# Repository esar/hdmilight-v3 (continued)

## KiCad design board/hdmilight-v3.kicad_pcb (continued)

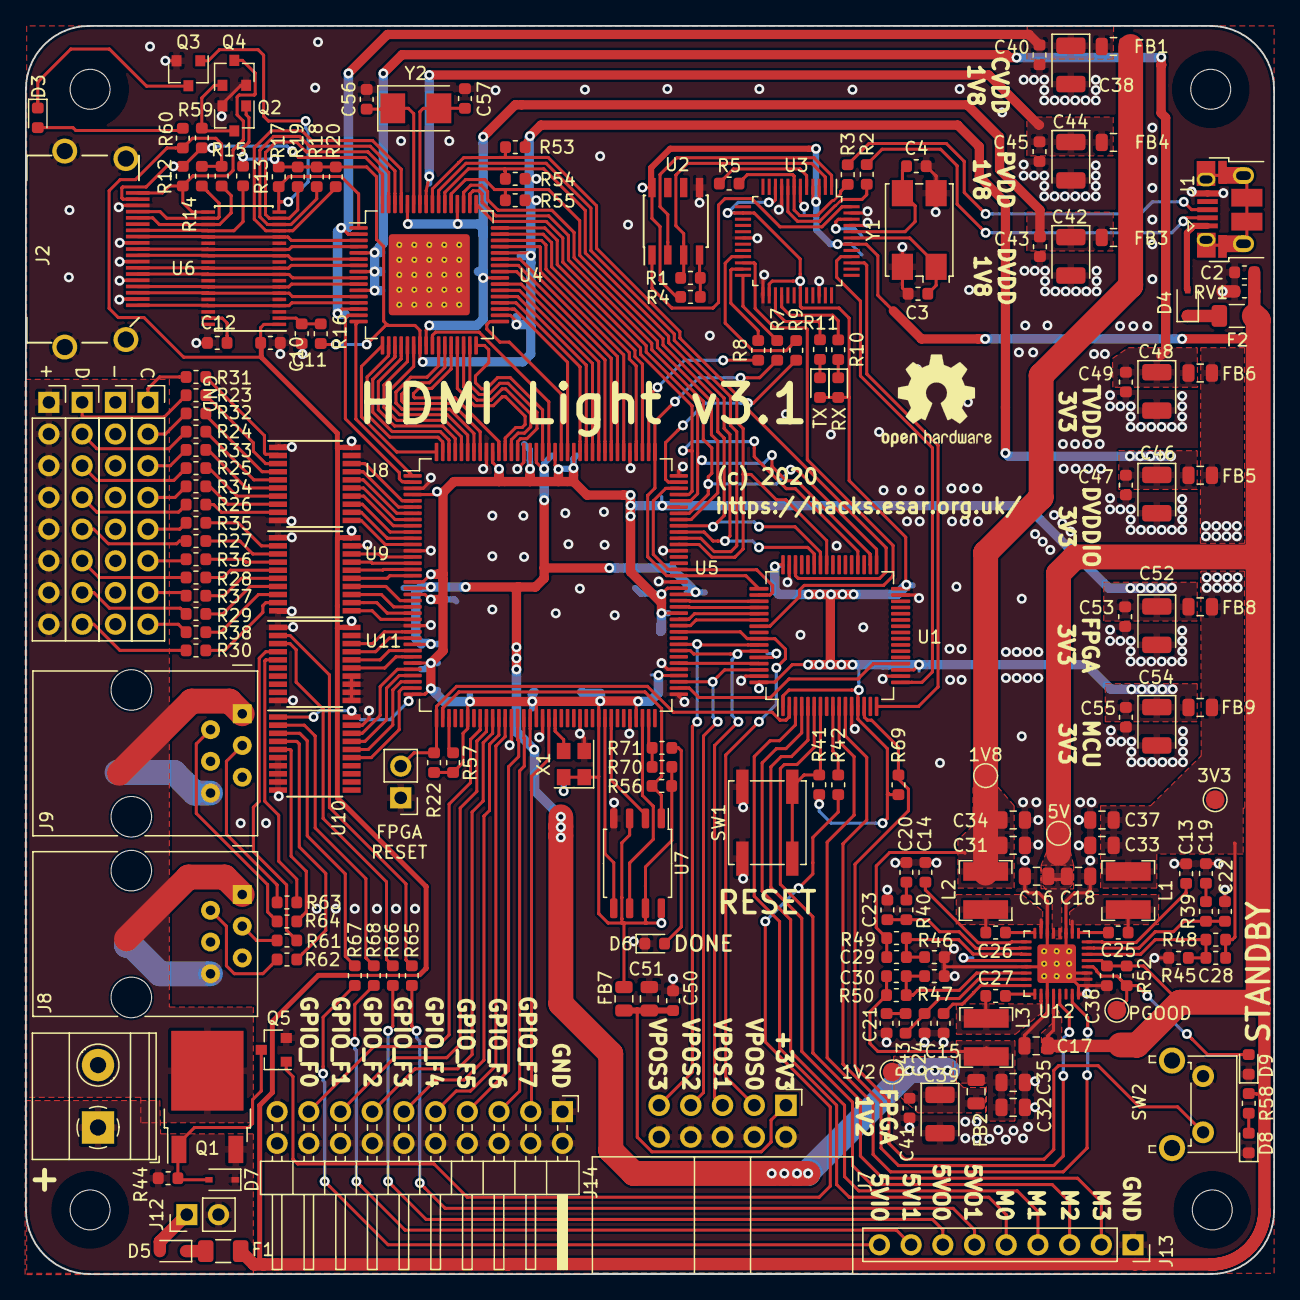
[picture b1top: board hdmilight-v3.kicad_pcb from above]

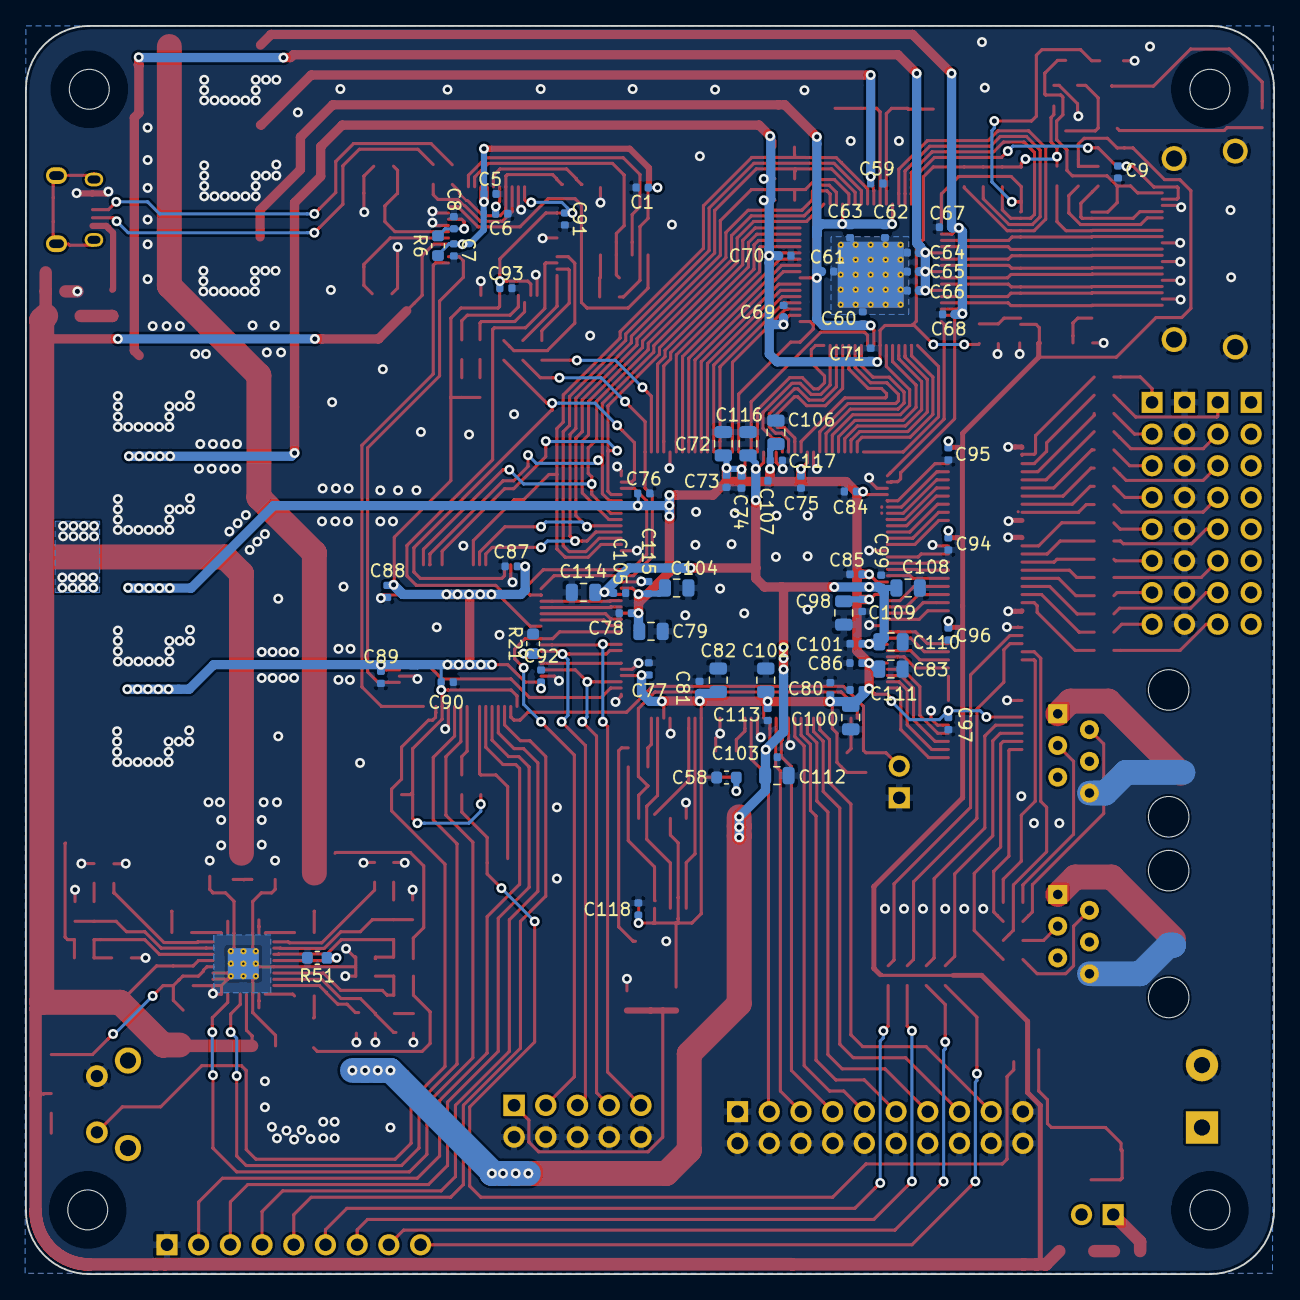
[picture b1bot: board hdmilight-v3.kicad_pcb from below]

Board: 2 copper layers, 100.0 x 100.0 mm, 259 parts (70 on the bottom side), 239 nets.

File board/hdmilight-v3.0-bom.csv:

Designator,Package,Quantity,Designation,Part #,Farnell #,Unit GBP,Total GBP
"C116,C114,C112,C110,C108,C106,C104,C102,C100,C98,C72,C83,C82,C79",C_0805_2012Metric,14,4.7uF,,,,0
"C117,C115,C113,C111,C109,C107,C105,C103,C101,C99,C86,C85,C84,C81,C80,C78,C77,C76,C75,C74,C73",C_0402_1005Metric,21,0.47uF,,,,0
"C19,C20,C21",C_0603_1608Metric,3,1nF,,,,0
"C22,C23,C24,C28,C29,C30",C_0603_1608Metric,6,DNI,,,,0
"C25,C26,C27",C_0603_1608Metric,3,0.047uF,,,,0
"C3,C4",C_0603_1608Metric,2,12pF,,,,0
C36,C_0603_1608Metric,1,2.2uF,,,,0
C37,C_0805_2012Metric,1,DNI,,,,0
"C38,C39,C42,C44,C46,C48,C52,C54",CP_EIA-3528-21_Kemet-B,8,33uF,Kemet: T491B336K006AT,2408593,0.396,3.168
"C50,C2,C10,C11,C12,C13,C14,C15,C40,C41,C43,C45,C47,C49,C53,C55",C_0603_1608Metric,16,0.1uF,,,,0
"C51,C16,C17,C18,C31,C32,C33,C34,C35",C_0805_2012Metric,9,22uF,TDK: C2012X5R1A226M085AC,2526256,0.493,4.437
"C57,C56",C_0603_1608Metric,2,18pF,,,,0
C58,C_0603_1608Metric,1,0.01uF,,,,0
"C9,C118,C1,C97,C96,C95,C94,C8,C6,C93,C91,C7,C5,C92,C90,C89,C88,C87,C71,C70,C69,C68,C67,C66,C65,C64,C63,C62,C61,C60,C59",C_0402_1005Metric,31,0.1uF,,,,0
"D5,D4",D_SOD-323,2,2A,"NXP: PMEG3020EJ,115",1757772,0.332,0.664
"D6,D3,D1,D2",LED_0603_1608Metric,4,LED,Kingbright: KPT-1608EC,2099221,0.107,0.428
D7,D_SOD-323,1,5V1,On Semi: MM3Z5V1ST1G,2317476,0.098,0.098
"F2,F1",Fuse_1206_3216Metric,2,1206L050,Littelfuse: 1206L050YR,1596993,0.285,0.57
"FB7,FB1,FB2,FB3,FB4,FB5,FB6,FB8,FB9",L_0805_2012Metric,9,22ohm@100MHz,Murata: BLM21PG220SN1D,1515659,0.055,0.495
J1,USB_Micro-B_Amphenol_10103594-0001LF_Horizontal,1,USB_B_Micro,Amphenol: 10103594-0001LF,2293752,0.44,0.44
"J10,J6,J5,J4",PinSocket_1x08_P2.54mm_Vertical,4,Conn_01x08,Multicomp: 2212S-08SG-85,1593463,0.17,0.68
J11,"TerminalBlock_Phoenix_MKDS-1,5-2_1x02_P5.00mm_Horizontal",1,Screw_Terminal_01x02,"Phoenix: MKDS 1,5/2",3714240,1.05,1.05
J12,PinHeader_1x02_P2.54mm_Horizontal,1,Conn_01x02_Male,Multicomp: MC34745,1593426,0.017,0.017
J13,PinHeader_1x16_P2.54mm_Horizontal,1,Conn_01x16_Male,Wurth: 61301611021,2356187,0.661,0.661
J2,HDMI_SOCKET_FCI_10029449,1,HDMI_A,Amphenol/FCI: 10029449-001RLF,2112524,1.22,1.22
J3,PinHeader_1x02_P2.54mm_Vertical,1,Conn_01x02_Male,Multicomp: 2211S-02G,1593411,0.011,0.011
J7,PinHeader_2x05_P2.54mm_Vertical,1,Conn_02x05_Odd_Even,Muticomp: 2213S-10G,1593442,0.053,0.053
"J8,J9",RJ12_Amphenol_54601,2,6P6C,Amphenol: 54601-906WPLF,2135977,0.265,0.53
"L1,L2",L_Bourns-SRN4018,2,4.7uH/2.1A,TDK: SPM4020T-4R7M-LR,2564035,1.52,3.04
L3,L_Bourns-SRN4018,1,2.2uH/3.5A,TDK: SPM4015T-2R2M-LR,2564023,0.342,0.342
Q1,TO-252-2,1,FDD6530A,On Semi: FDD6530A,3003908,0.759,0.759
"Q2,Q4,Q3",SOT-23,3,BSS123,On Semi: BSS123,9845321,0.254,0.762
R13,R_0603_1608Metric,1,27K,,,,0
"R14,R15,R18,R19,R20,R48,R51",R_0603_1608Metric,7,47K,,,,0
"R2,R3",R_0603_1608Metric,2,27R,,,,0
"R21,R1",R_0603_1608Metric,2,2K2,,,,0
R39,R_0603_1608Metric,1,15K,,,,0
R40,R_0603_1608Metric,1,33K,,,,0
R42,R_0603_1608Metric,1,150R,,,,0
R43,R_0603_1608Metric,1,18K,,,,0
R49,R_0603_1608Metric,1,20K,,,,0
R5,R_0603_1608Metric,1,1K5,,,,0
"R55,R54,R53",R_0603_1608Metric,3,4K7,,,,0
"R57,R56,R69,R44,R41,R4,R16,R45,R46,R47,R50,R52,R22",R_0603_1608Metric,13,10K,,,,0
"R59,R17",R_0603_1608Metric,2,100K,,,,0
R6,R_0603_1608Metric,1,470R,,,,0
"R68,R67,R66,R65,R64,R63,R62,R61,R23,R24,R25,R26,R27,R28,R29,R30,R31,R32,R33,R34,R35,R36,R37,R38",R_0603_1608Metric,24,82R,,,,0
"R7,R8,R9",R_0603_1608Metric,3,68R,,,,0
R70,R_0603_1608Metric,1,330R,,,,0
"R71,R60,R10,R11,R12",R_0603_1608Metric,5,1K,,,,0
RV1,R_0603_1608Metric,1,V5.5MLA0603H,Littelfuse: V5.5MLA0603H,1757273,0.36,0.36
SW1,SW_SPST_B3S-1000,1,SW_Push,Omron: B3S-1000,177807,0.535,0.535
SW2,SW_Tactile_SPST_Angled_PTS645Vx31-2LFS,1,SW_Push,C&K: PTS645VH58-2LFS,2320088,0.201,0.201
U1,LQFP-64_10x10mm_P0.5mm,1,STM32F303RETx,ST Micro: STM32F303RET6,2466939,6.56,6.56
U12,QFN-32-1EP_5x5mm_P0.5mm_EP3.1x3.1mm_ThermalVias,1,TPS65266,Texas: TPS65266RHBT,2471151,3.92,3.92
U2,SOIC-8_3.9x4.9mm_P1.27mm,1,93CxxB,Microchip: 93C46BT-I/SN,1607557,0.18,0.18
U3,LQFP-48_7x7mm_P0.5mm,1,FT2232D,FTDI: FT2232D,1615843,5.7,5.7
U4,LQFP-64-1EP_10x10mm_P0.5mm_EP6.5x6.5mm_ThermalVias,1,ADV7611,Analog: ADV7611,,6.5,6.5
U5,TQFP-144_20x20mm_P0.5mm,1,XC6SLX9-TQG144,Xilinx: XC6SLX9-2TQG144C,2763358,14.91,14.91
U6,TSSOP-38_4.4x9.7mm_P0.5mm,1,TPD12S520,Texas: TPD12S520DBTR,3116492,1.19,1.19
U7,SOIC-8_3.9x4.9mm_P1.27mm,1,S25FL064L,Cypress: S25FL064LABMFI010,2768034,1.68,1.68
"U8,U9,U10,U11",TSSOP-20_4.4x6.5mm_P0.65mm,4,74LV245,Texas: SN74LV245APWR,2342392,0.626,2.504
X1,Oscillator_SMD_Abracon_ASE-4Pin_3.2x2.5mm,1,SG-310SCF-32MHz,Multicomp: MCSJK-3N-32.00-3.3-25-B,2854318,0.639,0.639
Y1,Crystal_SMD_7050-4Pin_7.0x5.0mm,1,6MHz / 12pF,Euroquartz: 6.000MHZ MQ/30/30/-40+90/12PF,1640909,1.73,1.73
Y2,Crystal_SMD_5032-2Pin_5.0x3.2mm,1,28.6363MHz / 18pF,TXC: 7A-28.63636MAAJ-T,1841958,0.665,0.665
TOTAL,,244,,,,,66.699

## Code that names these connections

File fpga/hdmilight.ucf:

## Prohibit the automatic placement of pins that are connected to VCC or GND for configuration.
CONFIG PROHIBIT=P69;
CONFIG PROHIBIT=P60;

# Crystal Clock - use 32MHz onboard oscillator
NET "CLK" LOC = "P56" | IOSTANDARD = LVTTL | PERIOD = 31.25ns ;

NET "ADV_AP" LOC = "P105" | IOSTANDARD = LVTTL;
NET "ADV_SCLK" LOC = "P104" | IOSTANDARD = LVTTL;
NET "ADV_LRCLK" LOC = "P102" | IOSTANDARD = LVTTL;
NET "ADV_MCLK" LOC = "P101" | IOSTANDARD = LVTTL;

NET "ADV_SCL" LOC = "P100" | IOSTANDARD = LVCMOS33;
NET "ADV_SDA" LOC = "P99" | IOSTANDARD = LVCMOS33;
NET "ADV_INT1" LOC = "P98" | IOSTANDARD = LVCMOS33;
NET "ADV_RST" LOC = "P97" | IOSTANDARD = LVCMOS33;

NET "ADV_HS" LOC = "P112" | IOSTANDARD = LVTTL;
NET "ADV_VS" LOC = "P111" | IOSTANDARD = LVTTL;
NET "ADV_DE" LOC = "P114" | IOSTANDARD = LVTTL;
NET "ADV_LLC" LOC = "P126" | IOSTANDARD = LVCMOS33;

NET "ADV_P<0>" LOC = "P115" | IOSTANDARD = LVCMOS33;
NET "ADV_P<1>" LOC = "P116" | IOSTANDARD = LVCMOS33;
NET "ADV_P<2>" LOC = "P117" | IOSTANDARD = LVCMOS33;
NET "ADV_P<3>" LOC = "P118" | IOSTANDARD = LVCMOS33;
NET "ADV_P<4>" LOC = "P119" | IOSTANDARD = LVCMOS33;
NET "ADV_P<5>" LOC = "P120" | IOSTANDARD = LVCMOS33;
NET "ADV_P<6>" LOC = "P121" | IOSTANDARD = LVCMOS33;
NET "ADV_P<7>" LOC = "P123" | IOSTANDARD = LVCMOS33;
NET "ADV_P<8>" LOC = "P124" | IOSTANDARD = LVCMOS33;
NET "ADV_P<9>" LOC = "P127" | IOSTANDARD = LVCMOS33;
NET "ADV_P<10>" LOC = "P131" | IOSTANDARD = LVCMOS33;
NET "ADV_P<11>" LOC = "P132" | IOSTANDARD = LVCMOS33;
NET "ADV_P<12>" LOC = "P133" | IOSTANDARD = LVCMOS33;
NET "ADV_P<13>" LOC = "P134" | IOSTANDARD = LVCMOS33;
NET "ADV_P<14>" LOC = "P137" | IOSTANDARD = LVCMOS33;
NET "ADV_P<15>" LOC = "P138" | IOSTANDARD = LVCMOS33;
NET "ADV_P<16>" LOC = "P139" | IOSTANDARD = LVCMOS33;
NET "ADV_P<17>" LOC = "P140" | IOSTANDARD = LVCMOS33;
NET "ADV_P<18>" LOC = "P141" | IOSTANDARD = LVCMOS33;
NET "ADV_P<19>" LOC = "P142" | IOSTANDARD = LVCMOS33;
NET "ADV_P<20>" LOC = "P143" | IOSTANDARD = LVCMOS33;
NET "ADV_P<21>" LOC = "P144" | IOSTANDARD = LVCMOS33;
NET "ADV_P<22>" LOC = "P1" | IOSTANDARD = LVCMOS33;
NET "ADV_P<23>" LOC = "P2" | IOSTANDARD = LVCMOS33;

NET "LED_OUT<0>" LOC = "P6" | IOSTANDARD = LVCMOS33 | DRIVE = 2 | SLEW = SLOW;
NET "LED_OUT<1>" LOC = "P8" | IOSTANDARD = LVCMOS33 | DRIVE = 2 | SLEW = SLOW;
NET "LED_OUT<2>" LOC = "P10" | IOSTANDARD = LVCMOS33 | DRIVE = 2 | SLEW = SLOW;
NET "LED_OUT<3>" LOC = "P12" | IOSTANDARD = LVCMOS33 | DRIVE = 2 | SLEW = SLOW;
NET "LED_OUT<4>" LOC = "P15" | IOSTANDARD = LVCMOS33 | DRIVE = 2 | SLEW = SLOW;
NET "LED_OUT<5>" LOC = "P17" | IOSTANDARD = LVCMOS33 | DRIVE = 2 | SLEW = SLOW;
NET "LED_OUT<6>" LOC = "P22" | IOSTANDARD = LVCMOS33 | DRIVE = 2 | SLEW = SLOW;
NET "LED_OUT<7>" LOC = "P24" | IOSTANDARD = LVCMOS33 | DRIVE = 2 | SLEW = SLOW;

NET "LED_CLK<0>" LOC = "P5"  | IOSTANDARD = LVCMOS33 | DRIVE = 2 | SLEW = SLOW;
NET "LED_CLK<1>" LOC = "P7" | IOSTANDARD = LVCMOS33 | DRIVE = 2 | SLEW = SLOW;
NET "LED_CLK<2>" LOC = "P9" | IOSTANDARD = LVCMOS33 | DRIVE = 2 | SLEW = SLOW;
NET "LED_CLK<3>" LOC = "P11" | IOSTANDARD = LVCMOS33 | DRIVE = 2 | SLEW = SLOW;
NET "LED_CLK<4>" LOC = "P14" | IOSTANDARD = LVCMOS33 | DRIVE = 2 | SLEW = SLOW;
NET "LED_CLK<5>" LOC = "P16" | IOSTANDARD = LVCMOS33 | DRIVE = 2 | SLEW = SLOW;
NET "LED_CLK<6>" LOC = "P21" | IOSTANDARD = LVCMOS33 | DRIVE = 2 | SLEW = SLOW;
NET "LED_CLK<7>" LOC = "P23" | IOSTANDARD = LVCMOS33 | DRIVE = 2 | SLEW = SLOW;

NET FLASH_CS LOC="P38"  | IOSTANDARD=LVTTL | DRIVE=8 | SLEW=FAST;
NET FLASH_CK LOC="P70"  | IOSTANDARD=LVTTL | DRIVE=8 | SLEW=FAST;
NET FLASH_SI LOC="P64"  | IOSTANDARD=LVTTL | DRIVE=8 | SLEW=FAST;
NET FLASH_SO LOC="P65"  | IOSTANDARD=LVTTL | DRIVE=8 | SLEW=FAST | PULLUP;

NET "MCU_SPI_CLK" LOC = "P88" | IOSTANDARD = LVCMOS33;
NET "MCU_SPI_MISO" LOC = "P87" | IOSTANDARD = LVCMOS33;
NET "MCU_SPI_MOSI" LOC = "P85" | IOSTANDARD = LVCMOS33;
NET "MCU_SPI_CS" LOC = "P74" | IOSTANDARD = LVCMOS33;

NET "MCU_PD2" LOC = "P84" | IOSTANDARD = LVCMOS33;
NET "MCU_PB8" LOC = "P78" | IOSTANDARD = LVCMOS33;

NET "VIVEPOS_SENSOR<0>" LOC = "P83";
NET "VIVEPOS_SENSOR<1>" LOC = "P80";
NET "VIVEPOS_SENSOR<2>" LOC = "P75";
NET "VIVEPOS_SENSOR<3>" LOC = "P81";

NET "PAPIX_POS<0>" LOC = "P34";
NET "PAPIX_POS<1>" LOC = "P35";

NET "PAPIX_RGB<0>" LOC = "P29" | IOSTANDARD=LVCMOS33;
NET "PAPIX_RGB<1>" LOC = "P30" | IOSTANDARD=LVCMOS33;

NET "IN5V<0>" LOC = "P33";
NET "IN5V<1>" LOC = "P32";

NET "OUT5V<0>" LOC = "P26" | IOSTANDARD=LVCMOS33;
NET "OUT5V<1>" LOC = "P27" | IOSTANDARD=LVCMOS33;

NET "GPIO<0>" LOC = "P44" | IOSTANDARD = LVCMOS33;
NET "GPIO<1>" LOC = "P45" | IOSTANDARD = LVCMOS33;
NET "GPIO<2>" LOC = "P46" | IOSTANDARD = LVCMOS33;
NET "GPIO<3>" LOC = "P47" | IOSTANDARD = LVCMOS33;
NET "GPIO<4>" LOC = "P48" | IOSTANDARD = LVCMOS33;
NET "GPIO<5>" LOC = "P50" | IOSTANDARD = LVCMOS33;
NET "GPIO<6>" LOC = "P51" | IOSTANDARD = LVCMOS33;
NET "GPIO<7>" LOC = "P55" | IOSTANDARD = LVCMOS33;

NET "ROUTE_UNDER<0>" LOC = "P93"; // JTAG_TDO
NET "ROUTE_UNDER<1>" LOC = "P92"; // JTAG_TCK


NET "ADV_LLC" TNM_NET = "ADV_LLC";
TIMESPEC "TS_ADV_LLC" = PERIOD "ADV_LLC" 6 ns HIGH 50%;
NET "ADV_P<0>" OFFSET = IN 2.7 ns VALID 3.5 ns BEFORE "ADV_LLC" RISING;
NET "ADV_P<1>" OFFSET = IN 2.7 ns VALID 3.5 ns BEFORE "ADV_LLC" RISING;
NET "ADV_P<2>" OFFSET = IN 2.7 ns VALID 3.5 ns BEFORE "ADV_LLC" RISING;
NET "ADV_P<3>" OFFSET = IN 2.7 ns VALID 3.5 ns BEFORE "ADV_LLC" RISING;
NET "ADV_P<4>" OFFSET = IN 2.7 ns VALID 3.5 ns BEFORE "ADV_LLC" RISING;
NET "ADV_P<5>" OFFSET = IN 2.7 ns VALID 3.5 ns BEFORE "ADV_LLC" RISING;
NET "ADV_P<6>" OFFSET = IN 2.7 ns VALID 3.5 ns BEFORE "ADV_LLC" RISING;
NET "ADV_P<7>" OFFSET = IN 2.7 ns VALID 3.5 ns BEFORE "ADV_LLC" RISING;
NET "ADV_P<8>" OFFSET = IN 2.7 ns VALID 3.5 ns BEFORE "ADV_LLC" RISING;
NET "ADV_P<9>" OFFSET = IN 2.7 ns VALID 3.5 ns BEFORE "ADV_LLC" RISING;
NET "ADV_P<10>" OFFSET = IN 2.7 ns VALID 3.5 ns BEFORE "ADV_LLC" RISING;
NET "ADV_P<11>" OFFSET = IN 2.7 ns VALID 3.5 ns BEFORE "ADV_LLC" RISING;
NET "ADV_P<12>" OFFSET = IN 2.7 ns VALID 3.5 ns BEFORE "ADV_LLC" RISING;
NET "ADV_P<13>" OFFSET = IN 2.7 ns VALID 3.5 ns BEFORE "ADV_LLC" RISING;
NET "ADV_P<14>" OFFSET = IN 2.7 ns VALID 3.5 ns BEFORE "ADV_LLC" RISING;
NET "ADV_P<15>" OFFSET = IN 2.7 ns VALID 3.5 ns BEFORE "ADV_LLC" RISING;
NET "ADV_P<16>" OFFSET = IN 2.7 ns VALID 3.5 ns BEFORE "ADV_LLC" RISING;
NET "ADV_P<17>" OFFSET = IN 2.7 ns VALID 3.5 ns BEFORE "ADV_LLC" RISING;
NET "ADV_P<18>" OFFSET = IN 2.7 ns VALID 3.5 ns BEFORE "ADV_LLC" RISING;
NET "ADV_P<19>" OFFSET = IN 2.7 ns VALID 3.5 ns BEFORE "ADV_LLC" RISING;
NET "ADV_P<20>" OFFSET = IN 2.7 ns VALID 3.5 ns BEFORE "ADV_LLC" RISING;
NET "ADV_P<21>" OFFSET = IN 2.7 ns VALID 3.5 ns BEFORE "ADV_LLC" RISING;
NET "ADV_P<22>" OFFSET = IN 2.7 ns VALID 3.5 ns BEFORE "ADV_LLC" RISING;
NET "ADV_P<23>" OFFSET = IN 2.7 ns VALID 3.5 ns BEFORE "ADV_LLC" RISING;

NET "ambilight/hscale4/COUNT(0)" TNM_NET = "MC_GRP_FFS";
TIMESPEC "TS_MC_GRP_FFS" = FROM "MC_GRP_FFS" TO "MC_GRP_FFS" TS_ADV_LLC*2;
#NET "ambilight/hscale4/COUNT(0)" TNM_NET = RAMS "MC_GRP_RAMS";
#TIMESPEC "TS_MC_GRP_RAMS" = FROM "MC_GRP_RAMS" TO "MC_GRP_RAMS" TS_ADV_LLC*2;

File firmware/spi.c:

#include <stdint.h>
#include <stm32f303xe.h>
#include <core_cm4.h>
#include "printf.h"
#include "spi.h"



void spiInit()
{
	// Configure pins
	// PC10 = SPI3_SCLK
	// PC11 = SPI3_MISO
	// PC12 = SPI3_MOSI
	// PA4  = SPI3_NSS

	// Enable GPIOA
	RCC->AHBENR |= RCC_AHBENR_GPIOAEN;

	// Enable GPIOC
	RCC->AHBENR |= RCC_AHBENR_GPIOCEN;

	// Set pins mode to alternate function
	GPIOA->MODER &= ~GPIO_MODER_MODER4;
	GPIOA->MODER |= 2 << GPIO_MODER_MODER4_Pos;
	GPIOC->MODER &= ~(GPIO_MODER_MODER10 | GPIO_MODER_MODER11 | GPIO_MODER_MODER12);
	GPIOC->MODER |= (2 << GPIO_MODER_MODER10_Pos) | (2 << GPIO_MODER_MODER11_Pos) | (2 << GPIO_MODER_MODER12_Pos);

	// Set alternate function to SPI3
	// PC10 = SPI3_SCLK = Alt Func 6
	// PC11 = SPI3_MISO = Alt Func 6
	// PC12 = SPI3_MOSI = Alt Func 6
	// PA4  = SPI3_NSS  = Alt Func 6
	GPIOA->AFR[0] &= ~GPIO_AFRL_AFRL4;
	GPIOA->AFR[0] |= 6 << GPIO_AFRL_AFRL4_Pos;
	GPIOC->AFR[1] &= ~(GPIO_AFRH_AFRH2 | GPIO_AFRH_AFRH3 | GPIO_AFRH_AFRH4);
	GPIOC->AFR[1] |= (6 << GPIO_AFRH_AFRH2_Pos) | (6 << GPIO_AFRH_AFRH3_Pos) | (6 << GPIO_AFRH_AFRH4_Pos);

	// Set the drive strength for the pins
	GPIOA->OSPEEDR &= ~GPIO_OSPEEDER_OSPEEDR4;
	GPIOA->OSPEEDR |= 2 << GPIO_OSPEEDER_OSPEEDR4_Pos;
	GPIOC->OSPEEDR &= ~(GPIO_OSPEEDER_OSPEEDR10 | GPIO_OSPEEDER_OSPEEDR11 | GPIO_OSPEEDER_OSPEEDR12);
	GPIOC->OSPEEDR |= (2 << GPIO_OSPEEDER_OSPEEDR10_Pos) | (2 << GPIO_OSPEEDER_OSPEEDR11_Pos) | (2 << GPIO_OSPEEDER_OSPEEDR12_Pos);

	// Enable pull-up on SPI3_NSS pin
	GPIOA->PUPDR |= 1 << GPIO_PUPDR_PUPDR4_Pos;

	// Enable SPI3 Clock
	RCC->APB1ENR |= RCC_APB1ENR_SPI3EN;

	// Disable SPI3 for configuration and reset
	SPI3->CR1 &= ~SPI_CR1_SPE;
	RCC->APB1RSTR |= RCC_APB1RSTR_SPI3RST;
	RCC->APB1RSTR &= ~RCC_APB1RSTR_SPI3RST;

	// Set clock rate, polarity and phase
	SPI3->CR1 = (4 << SPI_CR1_BR_Pos) | SPI_CR1_CPOL | SPI_CR1_CPHA;

	// Set as master
	SPI3->CR1 |= SPI_CR1_MSTR;

	// Set RX threshold to 8-bits 
	// If we don't then trying to receive an odd number of bytes never completes
	SPI3->CR2 |= SPI_CR2_SSOE | SPI_CR2_FRXTH;
}

void spiTransaction(void* txBuf1, int txBuf1Len,
                    void* txBuf2, int txBuf2Len,
                    void* rxBuf, int rxBufLen)
{
	volatile uint8_t dummy;

	SPI3->SR &= ~SPI_SR_MODF;
	SPI3->CR1 |= SPI_CR1_SPE;
	SPI3->CR1 |= SPI_CR1_MSTR;

	while(txBuf1Len--)
	{
		while(!(SPI3->SR & SPI_SR_TXE))
			;
		*(uint8_t*)&SPI3->DR = *(uint8_t*)txBuf1++;
	}

	while(txBuf2Len--)
	{
		while(!(SPI3->SR & SPI_SR_TXE))
			;
		*(uint8_t*)&SPI3->DR = *(uint8_t*)txBuf2++;
	}

	// Wait for the TX buffer to empty
	while(SPI3->SR & SPI_SR_FTLVL)
		;

	// Wait for the bus to be idle
	while(SPI3->SR & SPI_SR_BSY)
		;

	// Clear any junk from the RX buffer
	while(SPI3->SR & SPI_SR_FRLVL)
		dummy = SPI3->DR;

	// Read data
	while(rxBufLen--)
	{
		// Send dummy byte to clock the data
		while(!(SPI3->SR & SPI_SR_TXE))
			;
		*(uint8_t*)&SPI3->DR = 0;

		// Wait for the data to arrive in the RX FIFO
		while(!(SPI3->SR & SPI_SR_FRLVL))
			;

		// Read it
		*(uint8_t*)rxBuf++ = SPI3->DR;
	}

	// Follow SPI shutdown procedure, probably unnecessary...
	// Wait for TX FIFO to be empty (should be already)
	while(SPI3->SR & SPI_SR_FTLVL)
		;

	// Wait for bus to be idle (should be already)
	while(SPI3->SR & SPI_SR_BSY)
		;

	// Disable SPI
	SPI3->CR1 &= ~SPI_CR1_SPE;

	// Clear any junk from the RX FIFO
	while(SPI3->SR & SPI_SR_FRLVL)
		dummy = SPI3->DR;

	// pretend we used the dummy value to silence the gcc warning
	(void)dummy;
}

void fpgaConfigWrite(uint16_t address, void* data, uint16_t length)
{
	uint8_t command[] = { 0x02, address >> 8, address & 0xff };
	spiTransaction(command, sizeof(command), data, length, NULL, 0);
}

void fpgaConfigRead(uint16_t address, void* data, uint16_t length)
{
	uint8_t command[] = { 0x01, address >> 8, address & 0xff, 0 };
	spiTransaction(command, sizeof(command), NULL, 0, data, length);
}

void fpgaConfigLoad(uint8_t slot)
{
	// TODO: Why does this need the last three bytes (1, 1, 0) ?
	uint8_t command[] = { 0xa0, slot + 1, 1, 1, 0 };
	spiTransaction(command, sizeof(command), NULL, 0, NULL, 0);
}

uint8_t fpgaConfigStatus()
{
	uint8_t status;
	uint8_t command[] = { 0xa2, 0 };
	spiTransaction(command, sizeof(command), NULL, 0, &status, sizeof(status));
	return status;
}

void fpgaFlashRead(uint32_t address, void* data, int length)
{
	uint8_t passthru_command[] = { 0xb0, 0 };
	uint8_t command[] = { 0x03, (address >> 16) & 0xff, (address >> 8) & 0xff, address & 0xff };
	spiTransaction(passthru_command, sizeof(passthru_command), NULL, 0, NULL, 0);
	spiTransaction(command, sizeof(command), NULL, 0, data, length);
}

void fpgaFlashWrite(uint32_t address, void* data, int length)
{
}

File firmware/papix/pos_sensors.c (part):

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	int i;

	// Configure pins
	// PB5 = TIM3_CH2 = Photo-diode 0
	// PB6 = TIM4_CH1 = Photo-diode 3
	// PB7 = TIM3_CH4 = Photo-diode 1
	// PB9 = TIM4_CH4 = Photo-diode 2

	// Enable GPIOB
	RCC->AHBENR |= RCC_AHBENR_GPIOBEN;
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	// PB4 = TIM3_CH1 = Alt Func 2
	GPIOB->AFR[0] &= ~GPIO_AFRH_AFRH5;
	GPIOB->AFR[0] |= 2 << GPIO_AFRH_AFRH5_Pos;
	// PB6 = TIM4_CH1 = Alt Func 2
	GPIOB->AFR[0] &= ~GPIO_AFRH_AFRH6;
	GPIOB->AFR[0] |= 2 << GPIO_AFRH_AFRH6_Pos;
	// PB7 = TIM3_CH4 = Alt Func 10
	GPIOB->AFR[0] &= ~GPIO_AFRL_AFRL7;
	GPIOB->AFR[0] |= 10 << GPIO_AFRH_AFRH7_Pos;
	// PB9 = TIM4_CH4 = Alt Func 2
	GPIOB->AFR[1] &= ~GPIO_AFRH_AFRH1;
	GPIOB->AFR[1] |= 2 << GPIO_AFRH_AFRH1_Pos;

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	RCC->APB1ENR |= RCC_APB1ENR_TIM4EN;

	// Set timer 3 channel inputs
	TIM3->CCMR1 = TIM_CCMR1_CC1S_1 |  // Channel1: TI2 (PB5)
	              TIM_CCMR1_CC2S_0 ;  // Channel2: TI2 (PB5)
	TIM3->CCMR2 = TIM_CCMR2_CC3S_1 |  // Channel3: TI4 (PB7)
	              TIM_CCMR2_CC4S_0 ;  // Channel4: TI4 (PB7)
	TIM3->CCER  = TIM_CCER_CC2P    |  // Channel2 active on falling edge
	              TIM_CCER_CC4P    |  // Channel4 active on falling edge
	              TIM_CCER_CC1E    |  // Enable channel 1
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	              TIM_CCER_CC4E    ;  // Enable channel 4

	// Set timer 4 channel inputs
	TIM4->CCMR1 = TIM_CCMR1_CC1S_0 |  // Channel1: TI1 (PB6)
	              TIM_CCMR1_CC2S_1 ;  // Channel2: TI1 (PB6)
	TIM4->CCMR2 = TIM_CCMR2_CC3S_1 |  // Channel3: TI4 (PB9)
	              TIM_CCMR2_CC4S_0 ;  // Channel4: TI4 (PB9)
	TIM4->CCER  = TIM_CCER_CC2P    |  // Channel2 active on falling edge
	              TIM_CCER_CC4P    |  // Channel4 active on falling edge
	              TIM_CCER_CC1E    |  // Enable channel 1
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
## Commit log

2019-11-01 Added first version of new all-in-one board
2019-11-03 Updated FPGA constraints, removed embedded AVR, added SPI access to config RAM
2019-11-14 Ported firmware to ARM (STM32F303RE) using SPI interface to FPGA
2019-11-14 Define all v3 FPGA connections
2020-05-08 Fixed bugs in v3.0 board:
    * Changed FPGA GPIO to 2 row with ground to make it compatible with logic analyser plug for debugging
    * Move position sensor from PB4 to PB5
    * Connect voltage regulator center pad to ground pins
    * Add SPI CS line between FPGA and MCU
    * Move HDMI hotplug LED back from board edge
    * Move HDMI ESD chip closer to connector
2020-05-08 Start integrating vivepos code
2020-05-08 Aded gerbers and schematic for v3.1 board
2020-05-10 Cleaned up makefiles, updated README
2020-05-10 Fixed booting FPGA from flash, needed to write .bin not .bit
2020-05-10 Added support for loading config from flash
2020-05-12 Added support for reading FPGA flash from MCU
2020-05-12 Fixed ADV and format change interrupt support for external MCU
2020-05-14 Fixed loading config on format change
2020-05-14 removed old unused silscreen labels
2020-05-14 Added v3.1 BOM
2020-05-15 Updated BOM with individual LED colours/types
2020-05-16 Fix level shifter part number 74LV245 -> 74LVC245
2020-05-16 Fixed overlapping silkscreen labels on back of board
2020-05-17 Update FPGA constraints for v3.1 board
2020-05-18 Fixed missing last byte when writing FPGA config via SPI
2020-05-19 BOM updates
    * Don't need EEPROM for FTDI
    * Change LED power switching transistor to the one I actually used
    * Sync CSV and interactive BOM files
2020-05-22 Implement standby button
2020-05-23 Fix LEDs lighting blue with no signal * Change HDMI config to default to 1920x1080 so that a default ambilight config will be matched * Fix LED power enable drive, now push-pull, was open-drain * Cha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
2020-05-23 Fixed interrupt related deadlocks
    Interrupt handlers use I2C and SPI comms with FPGA and ADV7611. If these occurred while other code
    was in the middle of a transaction then the I2C/SPI controller would be left in an unexpected
    state and the code could be left waiting for data to arrive that had already been flushed out
    Also, the STM32 doesn't support level triggered interrupts and it's possible to miss a rising-edge.
    Added a polling function to check for missed interrupts every 250ms. Without this there would
    be no more interrupts from the FPGA as it would wait forever for the missed one to be cleared
2020-05-31 Added missing bscan_spi_xc6slx9.bit file
2020-06-09 Add configuration doc, update readme
2020-06-11 configuration.md: fixed wrong origin
